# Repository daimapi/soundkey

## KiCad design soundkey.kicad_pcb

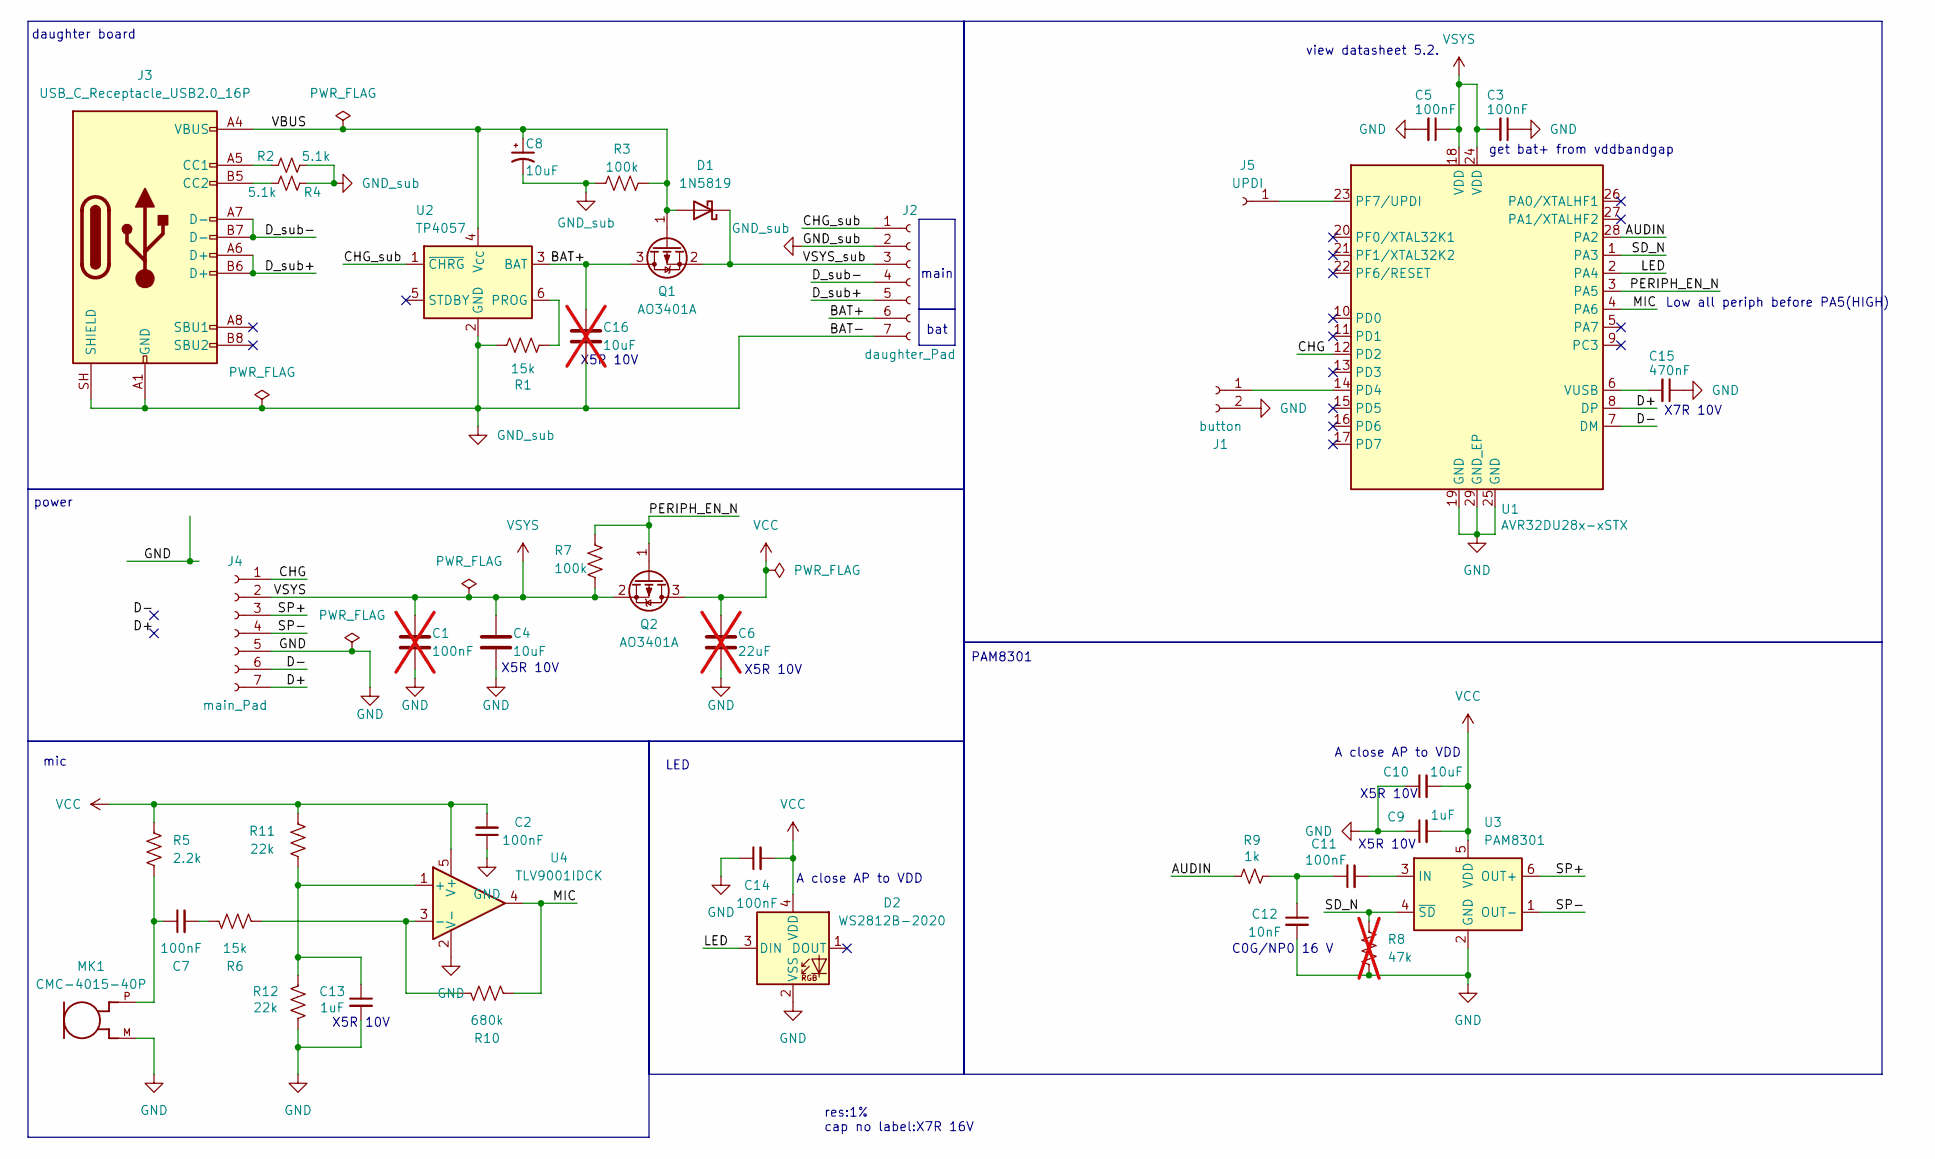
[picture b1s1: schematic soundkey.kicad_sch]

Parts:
C1: 100nF; C_0402_1005Metric; not fitted
C2, C3, C5, C14: 100nF; C_0402_1005Metric
C4, C10: 10uF; C_0805_2012Metric
C6: 22uF; C_1206_3216Metric; not fitted
C7, C11: 100nF; C_0603_1608Metric
C8: 10uF; C_Radial_D4.0mm_H5.0mm_P1.50mm
C9, C13: 1uF; C_0603_1608Metric
C12: 10nF; C_0402_1005Metric
C15: 470nF; C_0402_1005Metric
C16: 10uF; C_0805_2012Metric; not fitted
D1: 1N5819; D_DO-41_SOD81_P7.62mm_Horizontal
D2: WS2812B-2020; LED_WS2812B-2020_PLCC4_2.0x2.0mm
J1: button; SW_Kailh_KH
J2: daughter_Pad; Pad_7_1.5x2.0mm_G2.5mm
J3: USB_C_Receptacle_USB2.0_16P; USB_C_Receptacle_GCT_USB4105-xx-A_16P_TopMnt_Horizontal
J4: main_Pad; Pad_7_1.5x2.0mm_G2.5mm
J5: UPDI; TestPoint_Pad_D1.0mm
MK1: CMC-4015-40P; MIC_CMC-4015-40P; PART_REV 1.0
Q1, Q2: AO3401A; SOT-23
R1: 15k; R_Axial_DIN0204_L3.6mm_D1.6mm_P5.08mm_Horizontal
R2, R4: 5.1k; R_Axial_DIN0204_L3.6mm_D1.6mm_P5.08mm_Horizontal
R3: 100k; R_Axial_DIN0204_L3.6mm_D1.6mm_P5.08mm_Horizontal
R5: 2.2k; R_0402_1005Metric
R6: 15k; R_0402_1005Metric
R7: 100k; R_0402_1005Metric
R8: 47k; R_0402_1005Metric; not fitted
R9: 1k; R_0402_1005Metric
R10: 680k; R_0402_1005Metric
R11, R12: 22k; R_0402_1005Metric
U1: AVR32DU28x-xSTX; VQFN-28-1EP_4x4mm_P0.4mm_EP2.7x2.7mm_ThermalVias
U2: TP4057; TSOT-23-6
U3: PAM8301; SOT-23-6
U4: TLV9001IDCK; SOT-353_SC-70-5

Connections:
/AUDIN: R9.2, U1.28 (PA2)
/BAT+: C16.1, J2.6, Q1.3 (D), U2.3 (BAT)
/CHG: J4.1, U1.12 (PD2)
/CHG_sub: J2.1, U2.1 (~CHRG)
/D+: J4.7, U1.8 (DP)
/D-: J4.6, U1.7 (DM)
/D_sub+: J2.5, J3.A6 (D+), J3.B6 (D+)
/D_sub-: J2.4, J3.A7 (D-), J3.B7 (D-)
/LED: D2.3 (DIN), U1.2 (PA4)
/MIC: R10.1, U1.4 (PA6), U4.4
/PERIPH_EN_N: Q2.1 (G), R7.2, U1.3 (PA5)
/SD_N: R8.2, U1.1 (PA3), U3.4 (~SD)
/SP+: J4.3, U3.6 (OUT+)
/SP-: J4.4, U3.1 (OUT-)
/VBUS: C8.1, D1.2 (A), J3.A4 (VBUS), J3.A9 (VBUS), J3.B4 (VBUS), J3.B9 (VBUS), Q1.1 (G), R3.2, U2.4 (V_{CC})
/VSYS_sub: D1.1 (K), J2.3, Q1.2 (S)
GND: C1.2, C2.1, C3.1, C4.2, C5.2, C6.2, C9.1, C10.1, C12.2, C13.2, C14.1, C15.1, D2.2 (VSS), J1.2, J4.5, MK1.M, R8.1, R12.2, U1.19 (GND), U1.25 (GND), U1.29 (GND_EP), U3.2 (GND), U4.2 (V-)
GND_sub: C8.2, C16.2, J2.2, J2.7, J3.A1 (GND), J3.A12 (GND), J3.B1 (GND), J3.B12 (GND), J3.SH (SHIELD), R1.1, R2.1, R3.1, R4.2, U2.2 (GND)
unnamed: C7.1, MK1.P, R5.2
unnamed: C7.2, R6.2
unnamed: C11.1, C12.1, R9.1
unnamed: J1.1, U1.14 (PD4)
unnamed: J3.A5 (CC1), R2.2
unnamed: J3.B5 (CC2), R4.1
unnamed: J5.1 (Pin_1_1), U1.23 (PF7/UPDI)
unnamed: C15.2, U1.6 (VUSB)
unnamed: R1.2, U2.6 (PROG)
unnamed: C11.2, U3.3 (IN)
unnamed: C13.1, R11.2, R12.1, U4.1 (+)
unnamed: R6.1, R10.2, U4.3 (-)
VCC: C2.2, C6.1, C9.2, C10.2, C14.2, D2.4 (VDD), Q2.3 (D), R5.1, R11.1, U3.5 (VDD), U4.5 (V+)
VSYS: C1.1, C3.2, C4.1, C5.1, J4.2, Q2.2 (S), R7.1, U1.18 (VDD), U1.24 (VDD)

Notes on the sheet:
PAM8301
X5R 10V
LED
view datasheet 5.2.
X7R 10V
res:1% cap no label:X7R 16V
get bat+ from vddbandgap
bat
power
mic
daughter board
Low all periph before PA5(HIGH)
A close AP to VDD
C0G/NP0 16 V
main

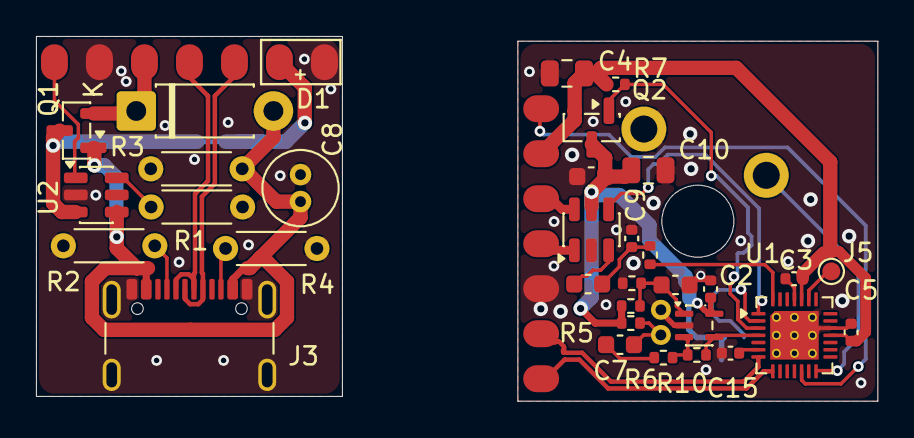
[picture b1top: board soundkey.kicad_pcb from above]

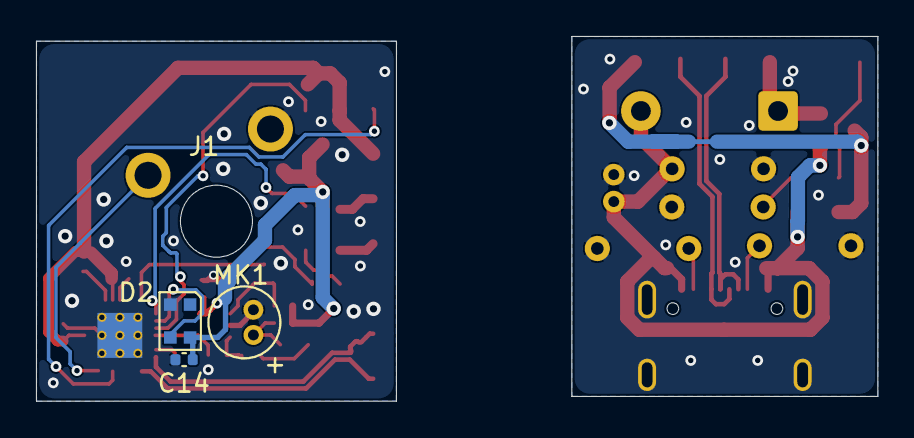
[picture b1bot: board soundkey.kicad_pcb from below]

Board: 2 copper layers, 46.7 x 20.3 mm, 38 parts (4 on the bottom side), 32 nets.

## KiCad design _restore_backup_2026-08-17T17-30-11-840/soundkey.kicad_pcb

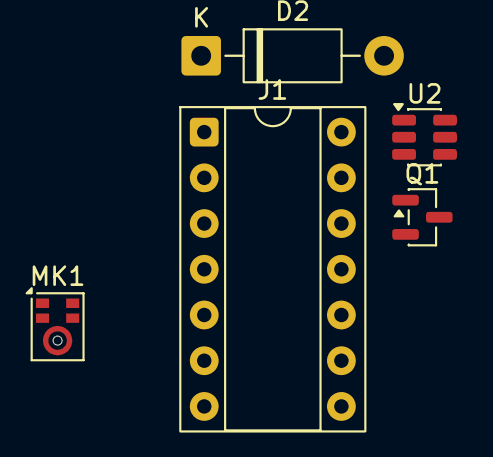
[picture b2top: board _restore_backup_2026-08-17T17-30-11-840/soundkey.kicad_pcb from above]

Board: 2 copper layers, 5 parts (0 on the bottom side), 3 nets, no tracks yet.

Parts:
D2: 1N5819; D_DO-41_SOD81_P10.16mm_Horizontal
J1: ISD1820; DIP-14_W7.62mm_Socket
MK1: SPH0641LU4H-1; Knowles_LGA-5_3.5x2.65mm
Q1: BSS84; SOT-23
U2: TP4057; TSOT-23-6

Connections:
/BAT+: Q1.3 (D), U2.3 (BAT)
/VBUS: D2.1 (K), Q1.2 (S)
/VCC: D2.2 (A), Q1.1 (G), U2.4 (V_{CC})
